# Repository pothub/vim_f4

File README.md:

Build and Test Environment based on Ubuntu 16.04 LTS for the My F4-Mini board

# 1. How to Setup the Environment
	sudo apt-get update
	sudo apt install gcc-arm-none-eabi
	sudo apt-get install python-serial
	sudo apt-get install cu
# 2. Usage
## 2.1 Build Project
	cd ~/main/
	make t
## 2.2 Flush Project
Change to STM32 uart write mode

Press the RESET while pressing the SW0

If write and view uart debug

	make f

If only write

	make ff

# 3. Source of
http://www.ktechinfowell.net/micromouse/index.html

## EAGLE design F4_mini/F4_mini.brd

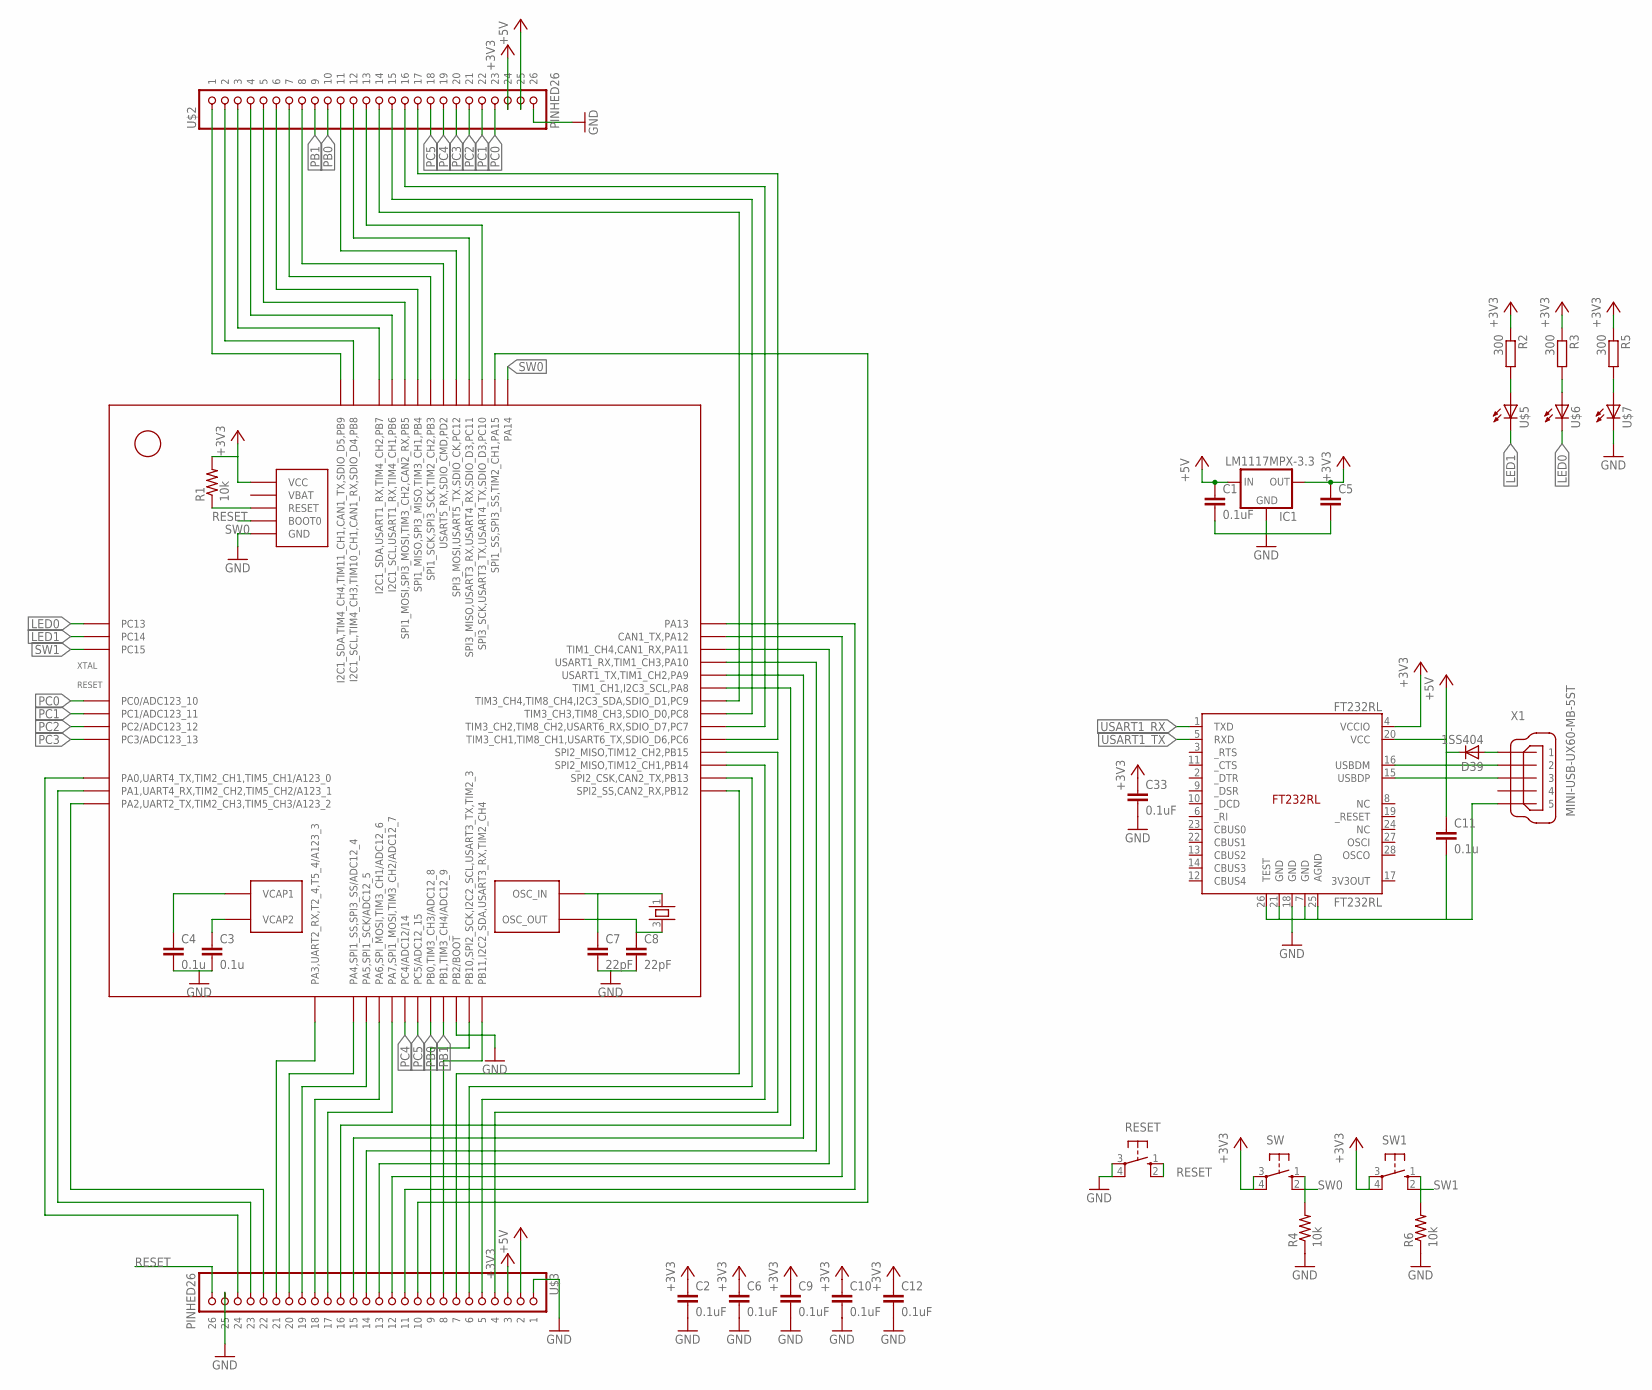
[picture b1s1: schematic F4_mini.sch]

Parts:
C1: 0.1uF; C0603K
C2, C6, C9, C10, C12, C33: 0.1uF; C0603
C3, C4, C11: 0.1u; C0603K
C5: C-EUC0603K; C0603K
C7, C8: 22pF; C0603K
D39: 1SS404; USC(1.25X2.5)
FT232RL: FT232RL; SSOP-28
IC1: LM1117MPX-3.3; SOT223
R1, R4, R6: 10k; R0603
R2, R3, R5: 300; R0603
RESET: 10-XX; B3F-10XX
SW, SW1: 10-XX; B3F-10XX
U$1: STM32F405_T; LQFP64
U$2, U$3: PINHED26
U$4: 25MHz; ASF
U$5, U$6, U$7: 0603
X1: MINI-USB-UX60-MB-5ST; UX60-MB-5ST

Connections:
+3V3: C2.1, C5.1, C6.1, C9.1, C10.1, C12.1, C33.1, FT232RL.4 (VCCIO), IC1.2 (OUT1), IC1.4 (OUT), R1.2, R2.1, R3.1, R5.1, SW.3, SW.4 (P1), SW1.3, SW1.4 (P1), U$1.13 (VCC), U$1.19 (VCC), U$1.32 (VCC), U$1.48 (VCC), U$1.64 (VCC), U$2.25 (24), U$3.4 (3)
+5V: C1.1, C11.1, D39.K (C), FT232RL.20 (VCC), IC1.3 (IN), U$2.26 (25), U$3.3 (2)
A: U$1.59 (I2C1_SDA,USART1_RX,TIM4_CH2,PB7), U$2.4 (3)
GND: C1.2, C2.2, C3.2, C4.2, C5.2, C6.2, C7.2, C8.2, C9.2, C10.2, C11.2, C12.2, C33.2, FT232RL.7 (GND), FT232RL.18 (GND), FT232RL.21 (GND), FT232RL.25 (AGND), FT232RL.26 (TEST), IC1.1 (GND), R4.1, R6.1, RESET.3, RESET.4 (P1), U$1.12 (GND), U$1.18 (GND), U$1.28 (PB2/BOOT), U$1.63 (GND), U$2.27 (26), U$3.2 (1), U$3.26 (25), U$7.C, X1.5
LED0: U$1.2 (PC13), U$6.C
LED1: U$1.3 (PC14), U$5.C
unnamed: R2.2, U$5.A
unnamed: U$1.16 (PA2,UART2_TX,TIM2_CH3,TIM5_CH3/A123_2), U$3.23 (22)
unnamed: U$1.14 (PA0,UART4_TX,TIM2_CH1,TIM5_CH1/A123_0), U$3.25 (24)
unnamed: U$1.15 (PA1,UART4_RX,TIM2_CH2,TIM5_CH2/A123_1), U$3.24 (23)
unnamed: U$1.41 (TIM1_CH1,I2C3_SCL,PA8), U$3.17 (16)
unnamed: U$1.22 (PA6,SPI_MOSI,TIM3_CH1/ADC12_6), U$3.19 (18)
unnamed: U$1.21 (PA5,SPI1_SCK/ADC12_5), U$3.20 (19)
unnamed: U$1.20 (PA4,SPI1_SS,SPI3_SS/ADC12_4), U$3.21 (20)
unnamed: U$1.17 (PA3,UART2_RX,T2_4,T5_4/A123_3), U$3.22 (21)
unnamed: D39.A, X1.1
unnamed: R3.2, U$6.A
unnamed: R5.2, U$7.A
unnamed: U$1.44 (TIM1_CH4,CAN1_RX,PA11), U$3.14 (13)
unnamed: U$1.45 (CAN1_TX,PA12), U$3.13 (12)
unnamed: U$1.46 (PA13), U$3.12 (11)
unnamed: U$1.23 (PA7,SPI1_MOSI,TIM3_CH2/ADC12_7), U$3.18 (17)
unnamed: U$1.61 (I2C1_SCL,TIM4_CH3,TIM10_CH1,CAN1_RX,SDI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), U$2.3 (2)
unnamed: U$1.62 (I2C1_SDA,TIM4_CH4,TIM11_CH1,CAN1_TX,SDI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), U$2.2 (1)
unnamed: U$1.34 (SPI2_CSK,CAN2_TX,PB13), U$3.7 (6)
unnamed: U$1.33 (SPI2_SS,CAN2_RX,PB12), U$3.8 (7)
unnamed: U$1.30 (PB11,I2C2_SDA,USART3_RX,TIM2_CH4), U$3.9 (8)
unnamed: U$1.29 (PB10,SPI2_SCK,I2C2_SCL,USART3_TX,TIM2_3), U$3.10 (9)
unnamed: U$1.50 (SPI1_SS,SPI3_SS,TIM2_CH1,PA15), U$3.11 (10)
unnamed: U$1.58 (I2C1_SCL,USART1_RX,TIM4_CH1,PB6), U$2.5 (4)
unnamed: U$1.57 (SPI1_MOSI,SPI3_MOSI,TIM3_CH2,CAN2_RX,PB5), U$2.6 (5)
unnamed: U$1.56 (SPI1_MISO,SPI3_MISO,TIM3_CH1,PB4), U$2.7 (6)
unnamed: U$1.55 (SPI1_SCK,SPI3_SCK,TIM2_CH2,PB3), U$2.8 (7)
unnamed: U$1.54 (USART5_RX,SDIO_CMD,PD2), U$2.9 (8)
unnamed: U$1.53 (SPI3_MOSI,USART5_TX,SDIO_CK,PC12), U$2.12 (11)
unnamed: U$1.52 (SPI3_MISO,USART3_RX,USART4_RX,SDIO_D3,P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), U$2.13 (12)
unnamed: U$1.51 (SPI3_SCK,USART3_TX,USART4_TX,SDIO_D3,PC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), U$2.14 (13)
unnamed: C3.1, U$1.47 (VCAP2)
unnamed: C4.1, U$1.31 (VCAP1)
unnamed: U$1.40 (TIM3_CH4,TIM8_CH4,I2C3_SDA,SDIO_D1,PC9), U$2.15 (14)
unnamed: C7.1, U$1.5 (OSC_IN), U$4.1
unnamed: C8.1, U$1.6 (OSC_OUT), U$4.3
unnamed: U$1.39 (TIM3_CH3,TIM8_CH3,SDIO_D0,PC8), U$2.16 (15)
unnamed: U$1.38 (TIM3_CH2,TIM8_CH2,USART6_RX,SDIO_D7,PC7), U$2.17 (16)
unnamed: FT232RL.16 (USBDM), X1.2
unnamed: FT232RL.15 (USBDP), X1.3
unnamed: U$1.37 (TIM3_CH1,TIM8_CH1,USART6_TX,SDIO_D6,PC6), U$2.18 (17)
PB0: U$1.26 (PB0,TIM3_CH3/ADC12_8), U$2.11 (10)
PB1: U$1.27 (PB1,TIM3_CH4/ADC12_9), U$2.10 (9)
PB14: U$1.35 (SPI2_MISO,TIM12_CH1,PB14), U$3.6 (5)
PB15: U$1.36 (SPI2_MISO,TIM12_CH2,PB15), U$3.5 (4)
PC0: U$1.8 (PC0/ADC123_10), U$2.24 (23)
PC1: U$1.9 (PC1/ADC123_11), U$2.23 (22)
PC2: U$1.10 (PC2/ADC123_12), U$2.22 (21)
PC3: U$1.11 (PC3/ADC123_13), U$2.21 (20)
PC4: U$1.24 (PC4/ADC12/14), U$2.20 (19)
PC5: U$1.25 (PC5/ADC12_15), U$2.19 (18)
RESET: R1.1, RESET.1 (S), RESET.2 (S1), U$1.7 (RESET), U$3.27 (26)
SW0: R4.2, SW.1 (S), SW.2 (S1), U$1.49 (PA14), U$1.60 (BOOT0)
SW1: R6.2, SW1.1 (S), SW1.2 (S1), U$1.4 (PC15)
USART1_RX: FT232RL.1 (TXD), U$1.43 (USART1_RX,TIM1_CH3,PA10), U$3.15 (14)
USART1_TX: FT232RL.5 (RXD), U$1.42 (USART1_TX,TIM1_CH2,PA9), U$3.16 (15)

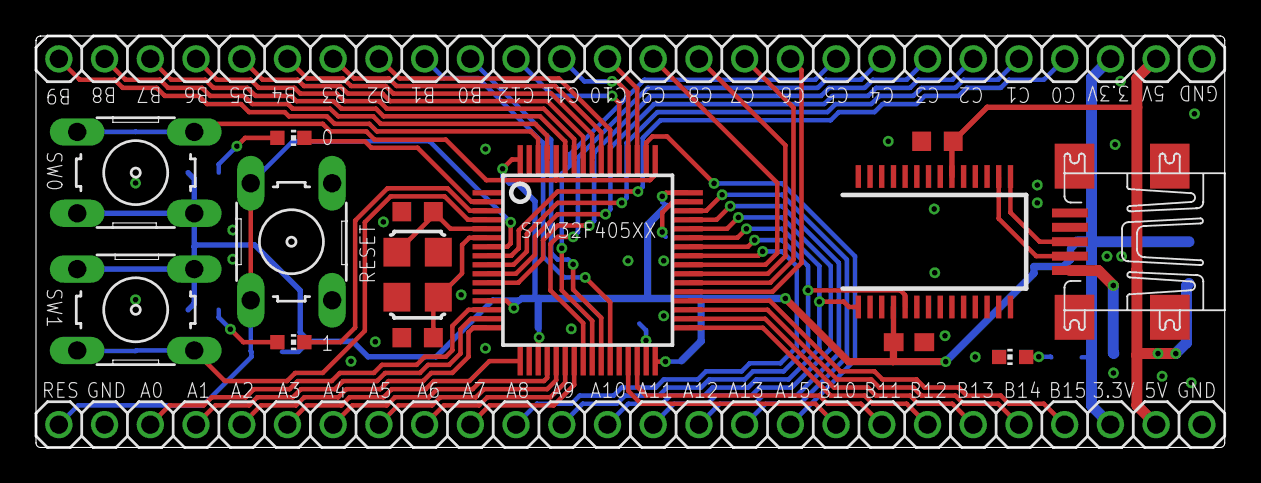
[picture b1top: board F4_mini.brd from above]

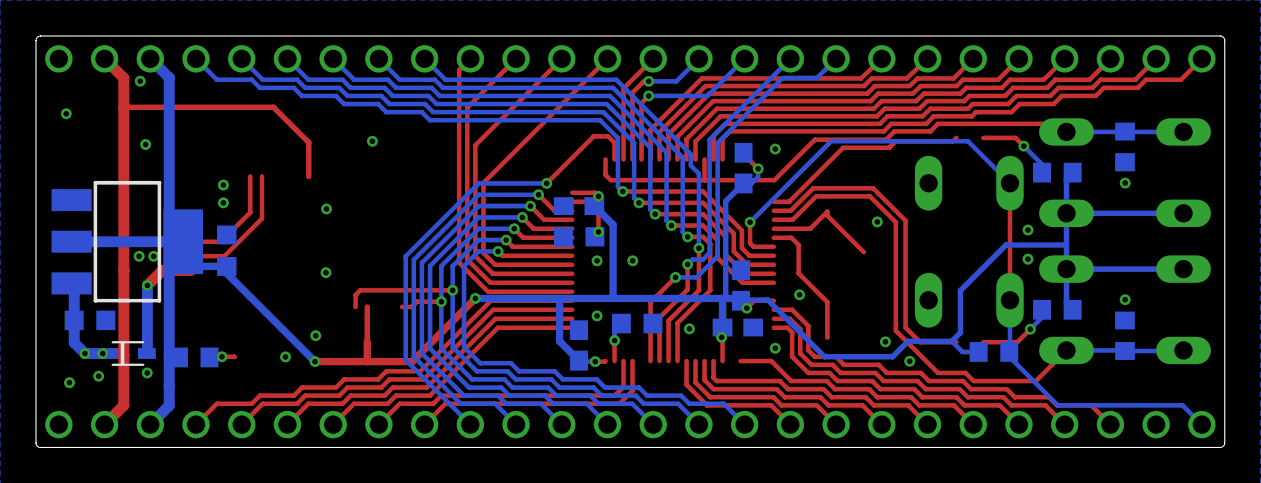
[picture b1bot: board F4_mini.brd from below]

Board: 2 copper layers, 66.0 x 22.9 mm, 33 parts (17 on the bottom side), 62 nets.

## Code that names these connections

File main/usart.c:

#include <stm32f4xx.h>

#define TRX_BUFFER_SIZE 64 // 送受信バッファサイズ
struct {
    unsigned int head, tail;
    char buff[TRX_BUFFER_SIZE];
} txb,rxb; // FIFOバッファ

DMA_InitTypeDef DMA_InitStructure_SIO_TX;

////////////////////////////////////////////////////////////////////////////////
/*
使用するペリフェラル
- USART1
- DMAC2-7 (TX)
- DMAC2-5 (RX)
使用するポート
- PA9 (USART1_TX)
- PA10 (USART1_RX)
*///////////////////////////////////////////////////////////////////////////////
#define DMAx_StreamY_SIO_TX        DMA2_Stream7
#define DMAx_StreamY_SIO_RX        DMA2_Stream5
#define DMA_Channel_x_SIO_TX       DMA_Channel_4
#define DMA_Channel_x_SIO_RX       DMA_Channel_4
void USART1_Conf(){
	RCC_APB2PeriphClockCmd(RCC_APB2Periph_USART1,ENABLE);
	RCC_AHB1PeriphClockCmd(RCC_AHB1Periph_DMA2, ENABLE);

	GPIO_PinAFConfig(GPIOA, GPIO_PinSource10, GPIO_AF_USART1);
	GPIO_PinAFConfig(GPIOA, GPIO_PinSource9, GPIO_AF_USART1);
	// Tx
	GPIO_InitTypeDef GPIO_InitStructure;
	GPIO_StructInit(&GPIO_InitStructure);
	GPIO_InitStructure.GPIO_Pin = GPIO_Pin_9;
	GPIO_InitStructure.GPIO_Mode = GPIO_Mode_AF;
	GPIO_InitStructure.GPIO_Speed = GPIO_Speed_100MHz;
	GPIO_InitStructure.GPIO_OType = GPIO_OType_PP;
	GPIO_InitStructure.GPIO_PuPd = GPIO_PuPd_NOPULL;
	GPIO_Init(GPIOA, &GPIO_InitStructure);
	// Rx
	GPIO_InitStructure.GPIO_Pin = GPIO_Pin_10;
	GPIO_InitStructure.GPIO_PuPd = GPIO_PuPd_UP;
	GPIO_Init(GPIOA, &GPIO_InitStructure);

	// USARTの設定
	USART_InitTypeDef USART_InitStructure;
	USART_StructInit(&USART_InitStructure);
	USART_InitStructure.USART_BaudRate = 115200;
	USART_InitStructure.USART_WordLength = USART_WordLength_8b;
	USART_InitStructure.USART_StopBits = USART_StopBits_1;
	USART_InitStructure.USART_Parity = USART_Parity_No;
	USART_InitStructure.USART_HardwareFlowControl = USART_HardwareFlowControl_None;
	USART_InitStructure.USART_Mode = USART_Mode_Rx | USART_Mode_Tx;
	USART_Init(USART1, &USART_InitStructure);
	
	// USART用DMAの初期化
	// 送信用
	DMA_StructInit(&DMA_InitStructure_SIO_TX);
	DMA_InitStructure_SIO_TX.DMA_Channel = DMA_Channel_x_SIO_TX;
	DMA_InitStructure_SIO_TX.DMA_PeripheralBaseAddr = (uint32_t)(&(USART1->DR));
	DMA_InitStructure_SIO_TX.DMA_Memory0BaseAddr = (uint32_t)txb.buff;
	DMA_InitStructure_SIO_TX.DMA_DIR = DMA_DIR_MemoryToPeripheral;
	DMA_InitStructure_SIO_TX.DMA_BufferSize = 0;
	DMA_InitStructure_SIO_TX.DMA_PeripheralInc = DMA_PeripheralInc_Disable;
	DMA_InitStructure_SIO_TX.DMA_MemoryInc = DMA_MemoryInc_Enable;
	DMA_InitStructure_SIO_TX.DMA_PeripheralDataSize = DMA_PeripheralDataSize_Byte;
	DMA_InitStructure_SIO_TX.DMA_MemoryDataSize = DMA_MemoryDataSize_Byte;
	DMA_InitStructure_SIO_TX.DMA_Mode = DMA_Mode_Normal;
	DMA_InitStructure_SIO_TX.DMA_Priority = DMA_Priority_Medium;
	DMA_InitStructure_SIO_TX.DMA_FIFOMode = DMA_FIFOMode_Disable;
	DMA_InitStructure_SIO_TX.DMA_MemoryBurst = DMA_MemoryBurst_Single;
	DMA_InitStructure_SIO_TX.DMA_PeripheralBurst = DMA_PeripheralBurst_Single;
	DMA_Init(DMAx_StreamY_SIO_TX, &DMA_InitStructure_SIO_TX);

	USART_DMACmd(USART1, USART_DMAReq_Tx, ENABLE);

	USART_Cmd(USART1, ENABLE);
}

////////////////////////////////////////////////////////////////////////////////
/** @brief 送信バッファに一文字追加する
@param[in] c 追加する文字
@return なし
*///////////////////////////////////////////////////////////////////////////////
//
void outbyte(char c)
{
// headに新しく追加する
// tailは次に送信されるデータを指す
// バッファに空きが無い（headがtailに追いついた）場合は待機する

	// バッファ内データ数をカウントし，空きがない場合待機する
	// バッファフルで待機しているときには割り込みを許可するためにwhileループになっている
	volatile int remain;
	while(1){
		// この関数は多重に実行されるとまずいので割り込みを禁止する
		__disable_irq();

		// DMACを一時的に停止
		DMA_Cmd(DMAx_StreamY_SIO_TX, DISABLE);
		while(DMA_GetCmdStatus(DMAx_StreamY_SIO_TX) != DISABLE);
		
		// 転送データ残数を取得
		remain = DMA_GetCurrDataCounter(DMAx_StreamY_SIO_TX);

		// バッファに空きがあればループから抜ける
		if(remain != TRX_BUFFER_SIZE) break;
		
		// DMAC動作再開
		DMA_DeInit(DMAx_StreamY_SIO_TX);
		DMA_InitStructure_SIO_TX.DMA_Memory0BaseAddr = (uint32_t)txb.buff;
		DMA_InitStructure_SIO_TX.DMA_BufferSize = TRX_BUFFER_SIZE;
		DMA_Init(DMAx_StreamY_SIO_TX, &DMA_InitStructure_SIO_TX);
		DMA_Cmd(DMAx_StreamY_SIO_TX, ENABLE);

		// 割り込み許可
		__enable_irq();

		// バッファに空きができるまで待機（この間割り込みが発生してもよい）
		while(DMA_GetCurrDataCounter(DMAx_StreamY_SIO_TX) == TRX_BUFFER_SIZE);
	}

	// ここの時点でDMACは停止，割り込みは禁止されている

	// 次に書き込もうとする領域がバッファ終端なら前に詰める
	if(txb.head == TRX_BUFFER_SIZE){
		int blank = TRX_BUFFER_SIZE - remain; // バッファの空き数
		int i;
		for(i=0;i+blank<TRX_BUFFER_SIZE;i++){
			txb.buff[i] = txb.buff[i+blank];
		}
		txb.head = i;
	}
	
	// 1文字追加
	txb.buff[txb.head++] = c;
	remain++;
	txb.tail = txb.head - remain;
	
	// DMACの再設定
	DMA_DeInit(DMAx_StreamY_SIO_TX);
	DMA_InitStructure_SIO_TX.DMA_Memory0BaseAddr = (uint32_t)(&txb.buff[txb.tail]);
	DMA_InitStructure_SIO_TX.DMA_BufferSize = remain;
	DMA_Init(DMAx_StreamY_SIO_TX, &DMA_InitStructure_SIO_TX);
	
	// DMAC動作再開
	DMA_Cmd(DMAx_StreamY_SIO_TX, ENABLE);
	
	// 割り込み許可
	__enable_irq();
}

////////////////////////////////////////////////////////////////////////////////
/** @brief 受信バッファから一文字取得する
@retval 読みだした文字（受信バッファに入力があるとき）
@return ヌル文字（受信バッファが空のとき）
*///////////////////////////////////////////////////////////////////////////////
volatile char inkey()
{
// head（DMACが受信データを書き込む位置）に新しく受信データが蓄積される．
// tailから読み出せばいい
// headがtailに追いつくとバッファオーバーフローとなり正しく読み出せない

	// この関数は多重に実行されるとまずいので割り込みを禁止する
	__disable_irq();
	
	// headの位置を読み取る
	rxb.head = TRX_BUFFER_SIZE - DMA_GetCurrDataCounter(DMAx_StreamY_SIO_RX);
	
	// バッファが空ならヌル文字を返す
	if(rxb.head == rxb.tail){
		// 割り込み許可
		__enable_irq();

		return '\0';
	}
	
	// バッファから一文字読み取り返す
	char c;
	c = rxb.buff[rxb.tail++];
	if(rxb.tail == TRX_BUFFER_SIZE) rxb.tail = 0;
	
	// 割り込み許可
	__enable_irq();
	
	return c;
}

////////////////////////////////////////////////////////////////////////////////
/** @brief 受信バッファを空にする
@return なし
*///////////////////////////////////////////////////////////////////////////////
void clear_rxb()
{
	while(inkey()!=0);
}

////////////////////////////////////////////////////////////////////////////////
/** @brief 受信バッファから一文字取得する（入力があるまで待つ）
@return 取得した文字
*///////////////////////////////////////////////////////////////////////////////
char inbyte()
{
	volatile char c;
	while((c = inkey()) == '\0');
	return c;
}

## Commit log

2016-02-05 first
2016-04-24 test
2016-04-24 add README
2016-04-24 README
